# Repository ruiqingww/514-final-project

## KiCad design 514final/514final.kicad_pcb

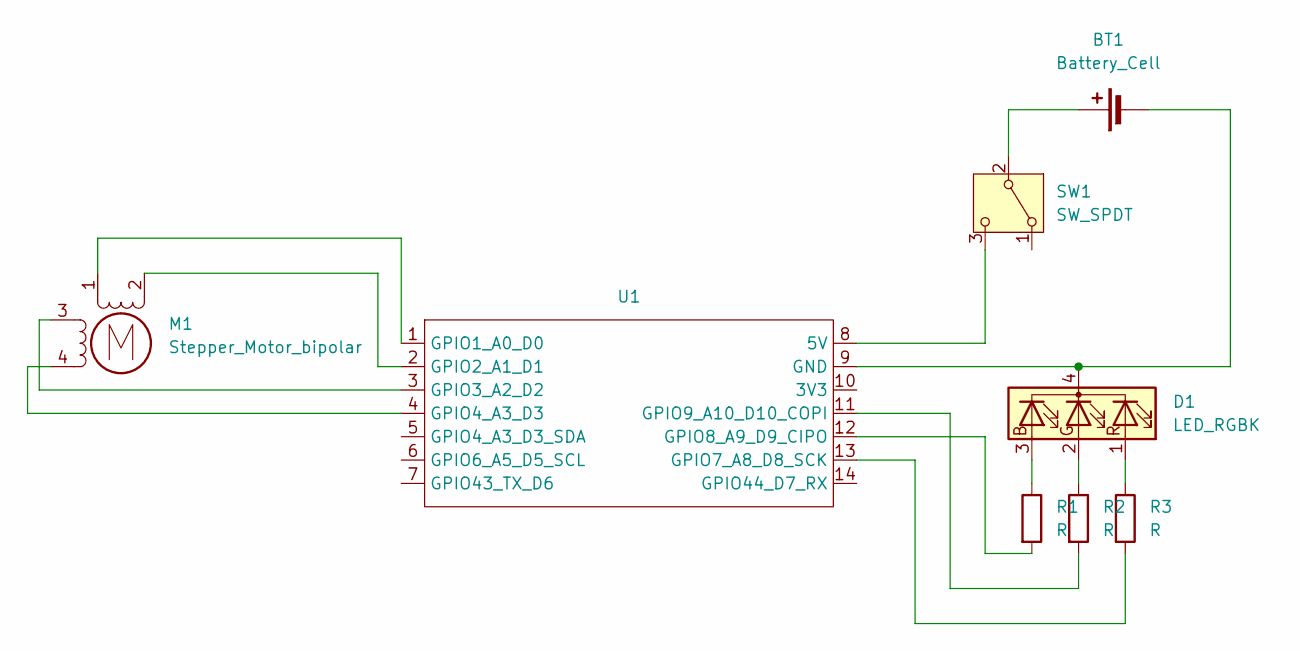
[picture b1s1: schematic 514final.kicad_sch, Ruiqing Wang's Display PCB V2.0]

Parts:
BT1: Battery_Cell; JST_NV_B02P-NV_1x02_P5.00mm_Vertical
D1: LED_RGBK; LED_D5.0mm-4_RGB_Staggered_Pins
M1: Stepper_Motor_bipolar; x27_stepper
R1, R2, R3: R; R_0805_2012Metric_Pad1.20x1.40mm_HandSolder
SW1: SW_SPDT; JST_EH_B3B-EH-A_1x03_P2.50mm_Vertical
U1: XIAO_ESP32_SENSE

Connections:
unnamed: BT1.1 (+), SW1.2 (B)
unnamed: BT1.2 (-), D1.4 (K), U1.9 (GND)
unnamed: D1.3 (BA), R1.1
unnamed: D1.2 (GA), R2.1
unnamed: D1.1 (RA), R3.1
unnamed: M1.2 (-), U1.2 (GPIO2_A1_D1)
unnamed: SW1.3 (C), U1.8 (5V)
unnamed: M1.1, U1.1 (GPIO1_A0_D0)
unnamed: M1.3, U1.3 (GPIO3_A2_D2)
unnamed: M1.4, U1.4 (GPIO4_A3_D3)
unnamed: R3.2, U1.13 (GPIO7_A8_D8_SCK)
unnamed: R1.2, U1.12 (GPIO8_A9_D9_CIPO)
unnamed: R2.2, U1.11 (GPIO9_A10_D10_COPI)

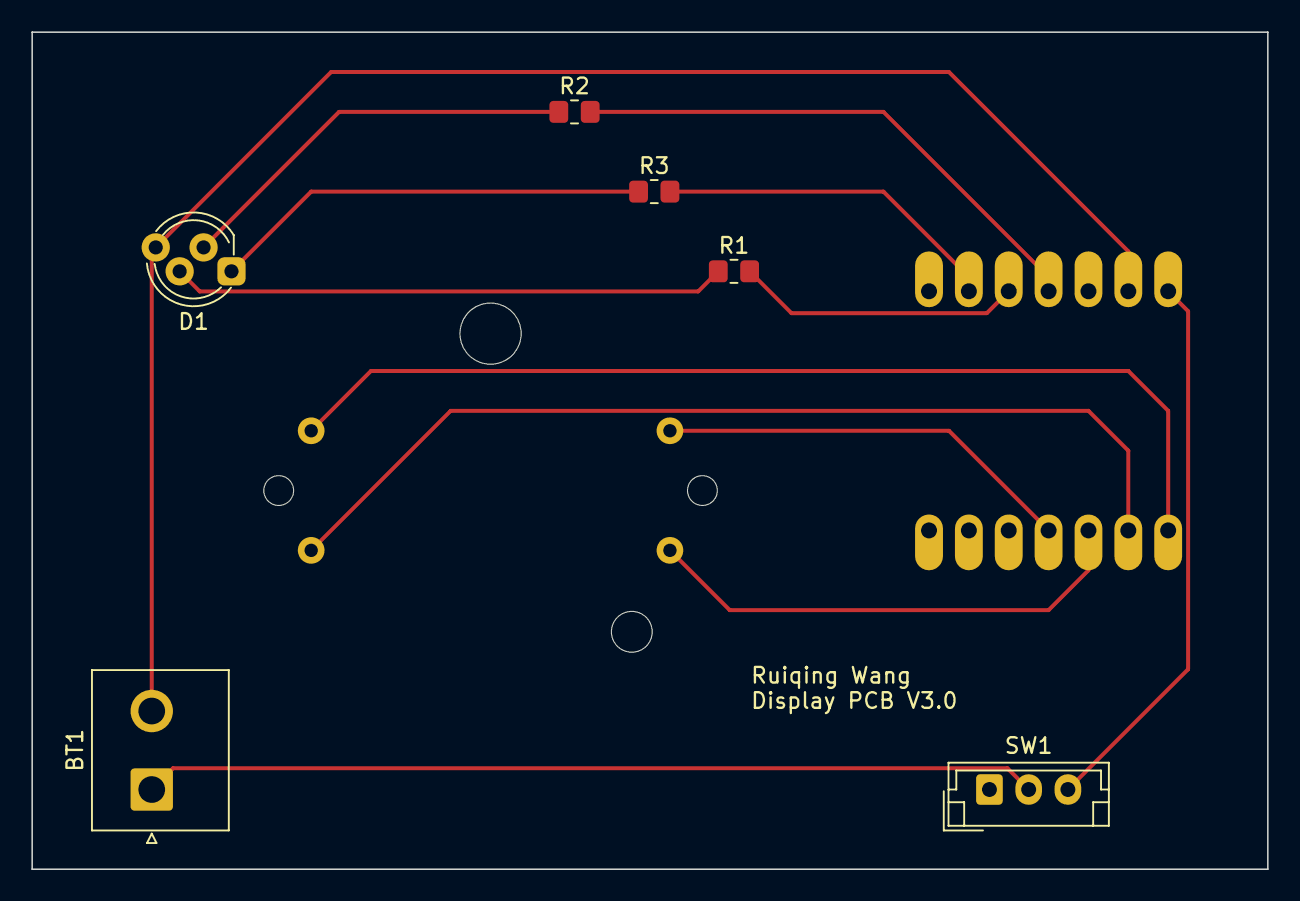
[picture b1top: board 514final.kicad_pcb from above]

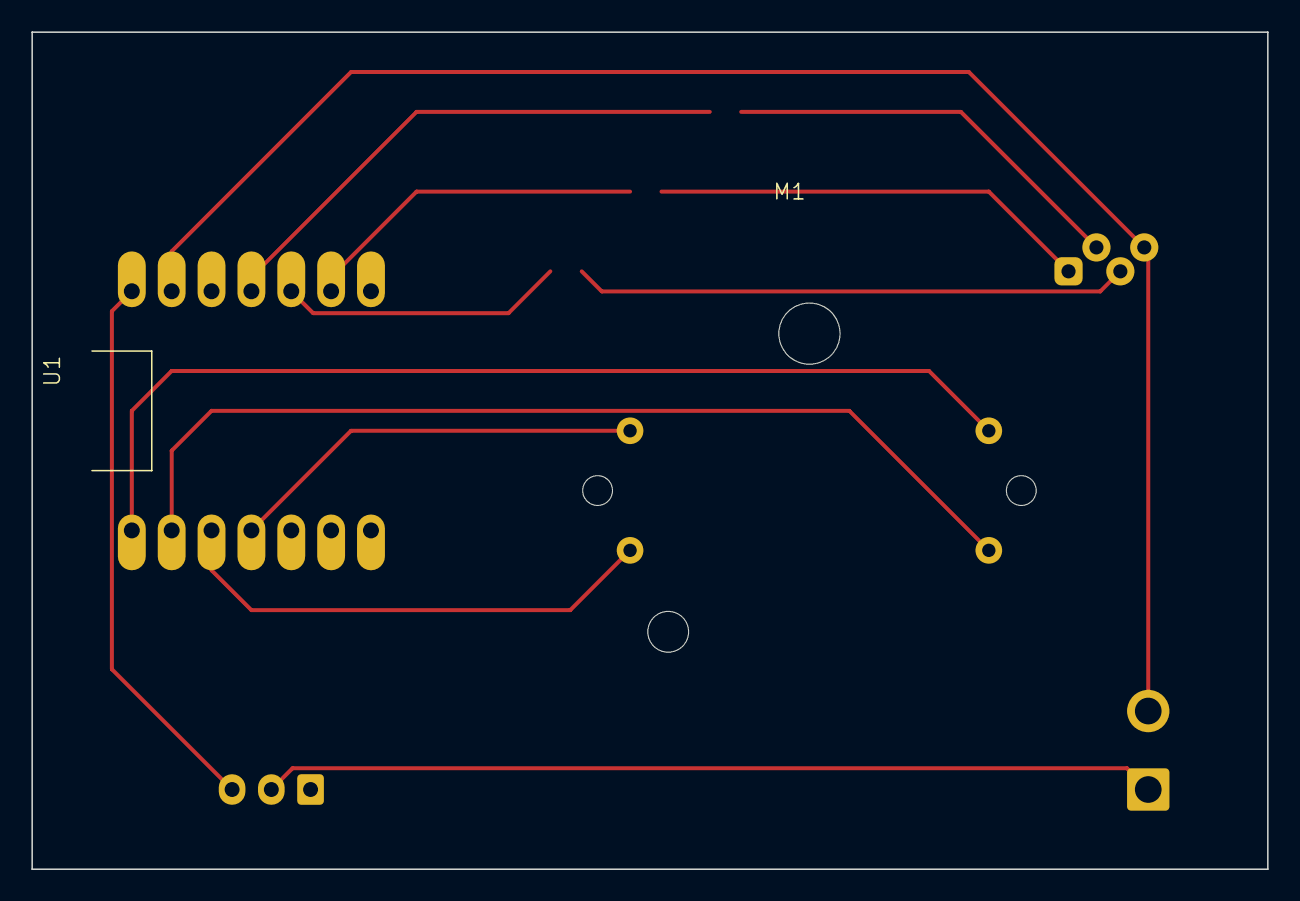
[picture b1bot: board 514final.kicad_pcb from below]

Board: 2 copper layers, 78.7 x 53.3 mm, 8 parts (2 on the bottom side), 13 nets.

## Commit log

2024-01-17 Add files via upload
    add diagram and datasheet
2024-01-17 delet file
2024-01-18 add pcb file
2024-02-04 v3.0
2024-02-07 add battery
2024-02-21 add code
2024-03-06 update code
2024-03-06 change file name
2024-03-06 add jpg
2024-03-07 final version
